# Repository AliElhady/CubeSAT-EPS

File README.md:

# CubeSAT-EPS
CubeSat Electrical Power System (EPS)

This project is a custom Electrical Power System for a CubeSat-class satellite, designed from scratch around a 2-cell Li-ion battery pack, solar input, and an STM32G474 microcontroller for smart power management and telemetry.

The EPS handles everything from harvesting solar energy, to charging and protecting the battery, to distributing clean, regulated rails to the rest of the satellite and streaming live power data to a ground station over LoRa.

Key Features

⚡ Solar Energy Harvesting & Battery Charging

MPPT-based solar charger (BQ24650 class) for 2S Li-ion pack
Supports simultaneous battery charging and system load powering
Automatic priority: uses solar power when available, falls back to battery when not

🔋 Battery Management & Protection

2-cell Li-ion battery pack with BMS for over-charge, over-discharge and over-current protection
Ideal-diode & reverse-polarity MOSFET circuitry on the battery input
TVS + LC filtering on critical power rails

📏 Power Monitoring & Telemetry

Multiple INA226 current/voltage monitors on battery, solar input, and main rails
Real-time telemetry sent via DL-SX1278PA LoRa module to a ground station
Designed for logging battery voltage, current, power, and solar harvesting performance

🧠 Control & Housekeeping

STM32G474RE microcontroller for EPS control, data acquisition, and LoRa communication
5 V and 3.3 V regulated rails for payload, OBC, and communication subsystems
Fault monitoring hooks for future safe-mode / load-shedding logic

🛠️ Hardware-Focused Design

KiCad-based 4-layer PCB (EPS + LoRa + sensing on a single board)
U.FL RF connector with optional π-network pads for antenna matching
Designed as a teaching/learning platform for small-sat power electronics

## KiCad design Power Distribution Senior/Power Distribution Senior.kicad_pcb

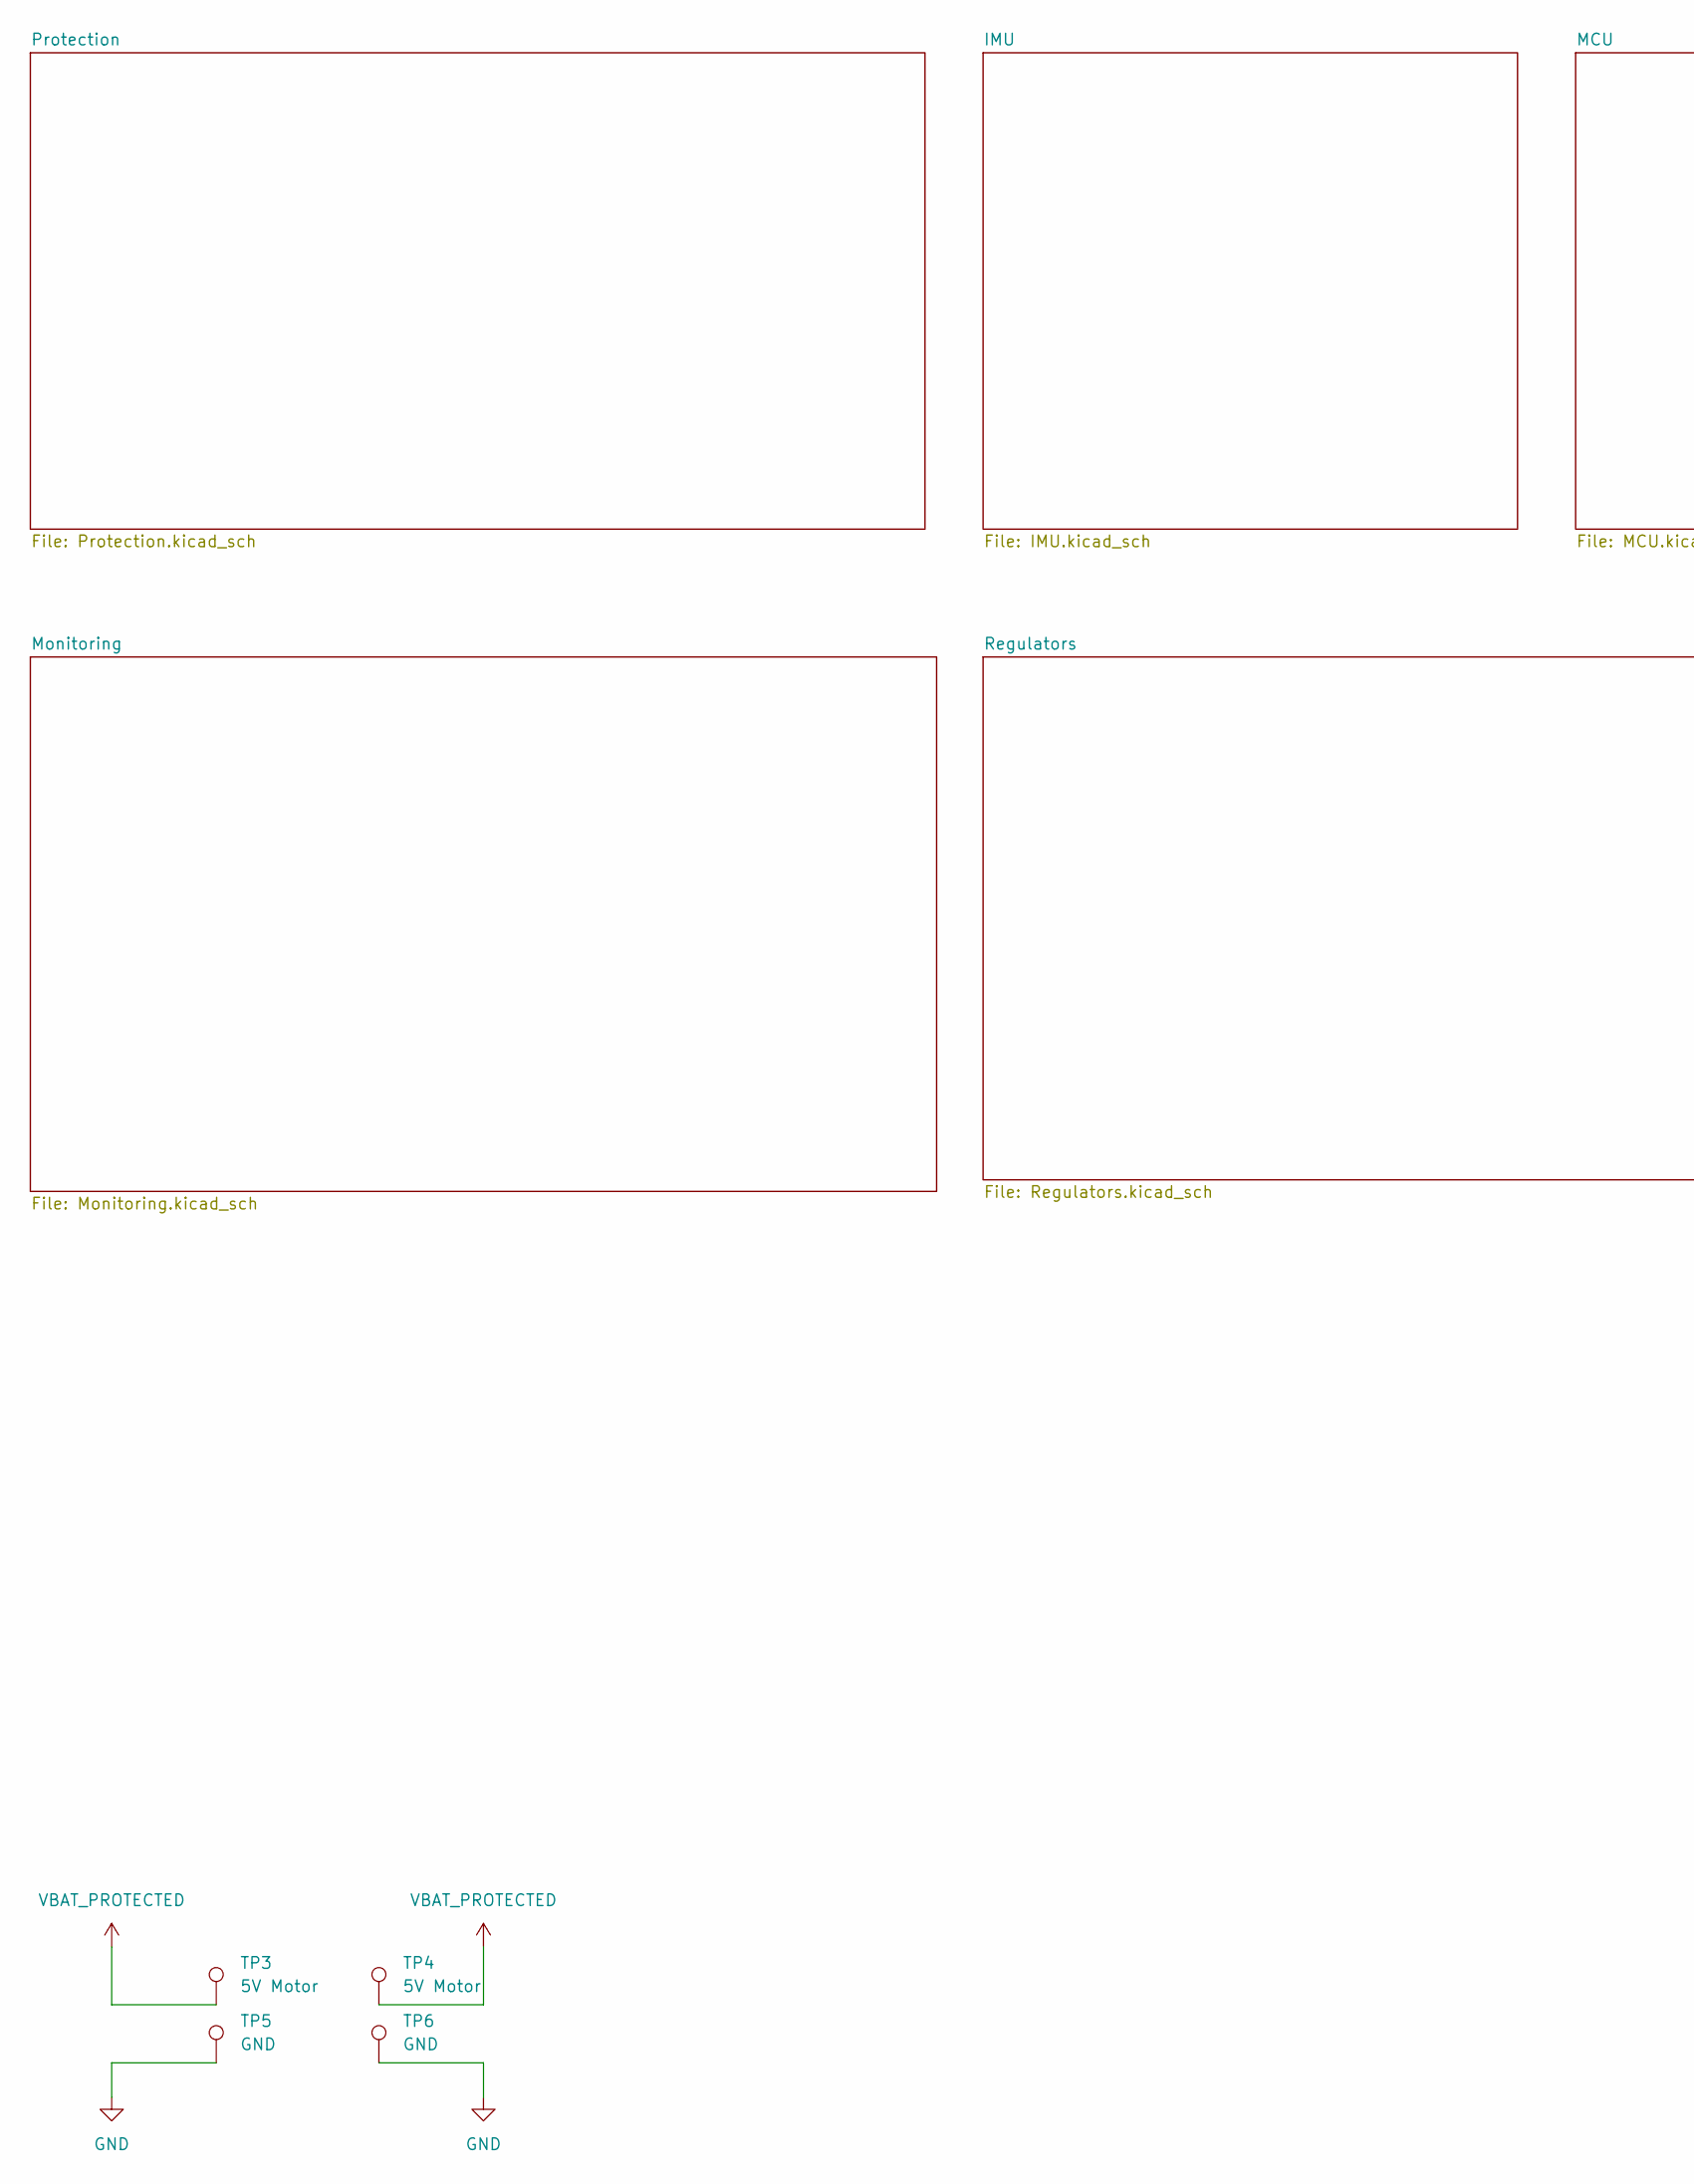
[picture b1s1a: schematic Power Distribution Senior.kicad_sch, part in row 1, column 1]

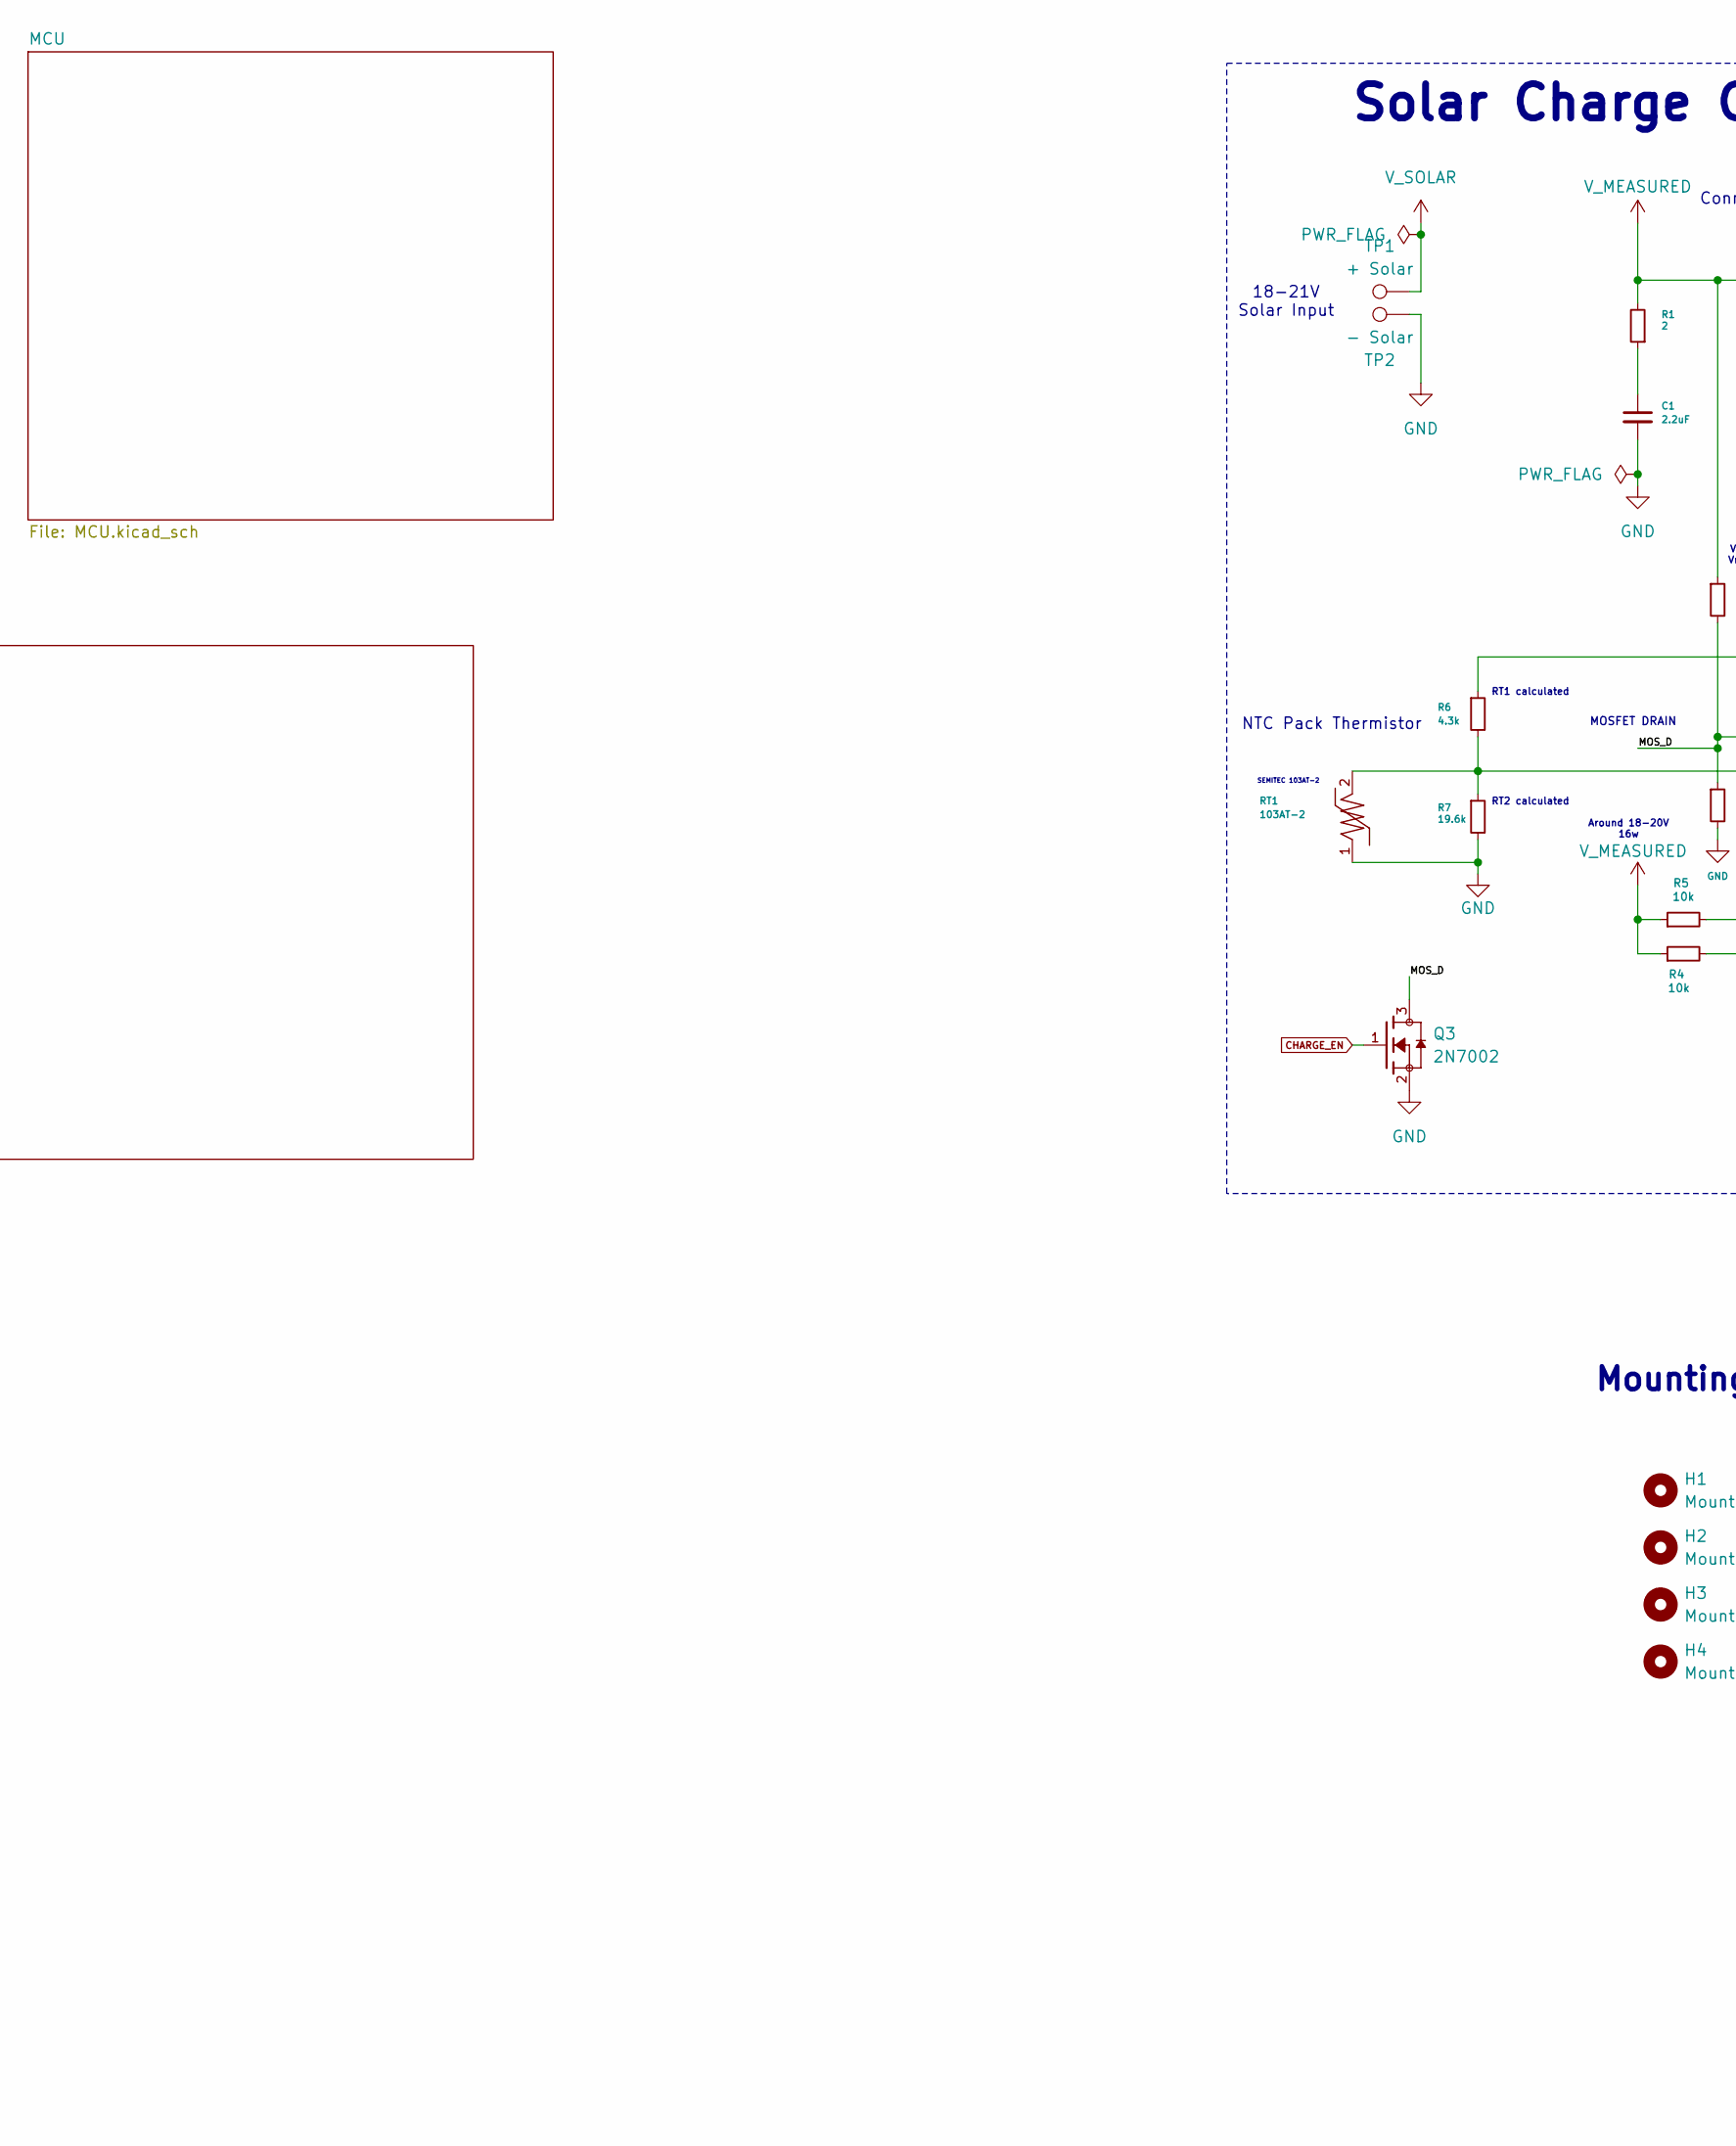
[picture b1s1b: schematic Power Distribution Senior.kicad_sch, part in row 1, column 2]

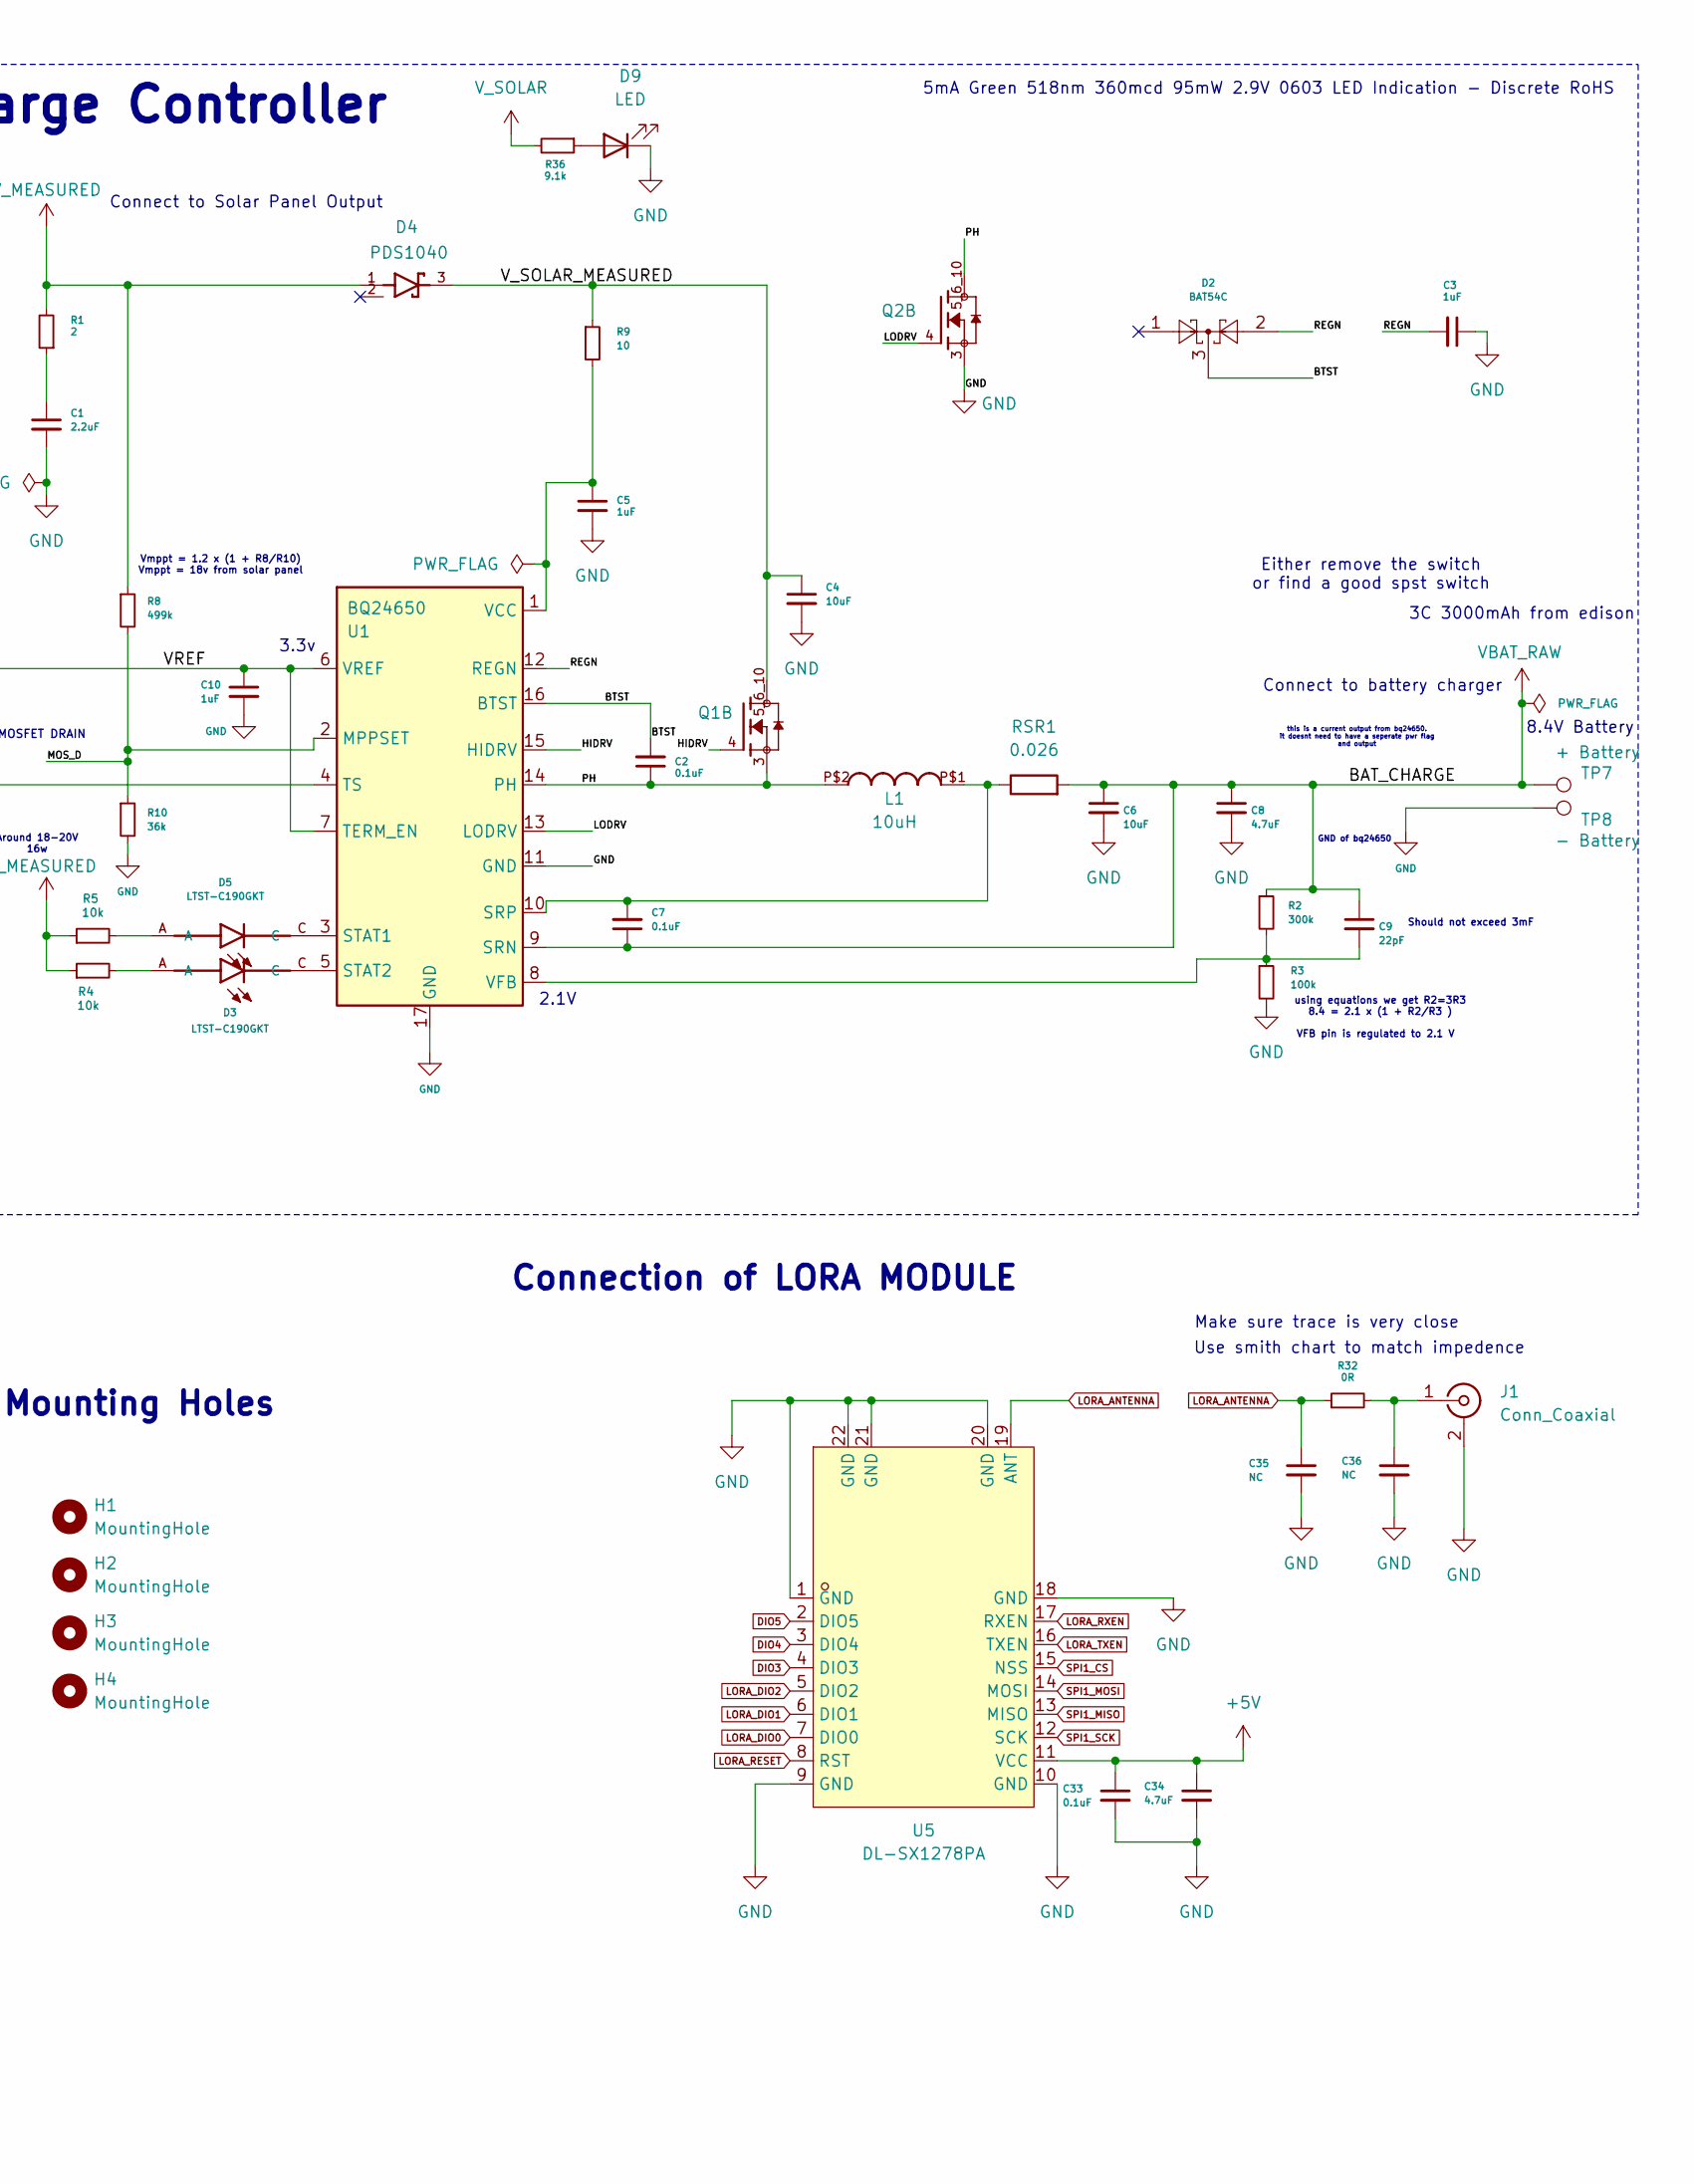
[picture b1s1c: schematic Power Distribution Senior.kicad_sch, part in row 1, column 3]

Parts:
C1: 2.2uF; C_1206_3216Metric
C2, C7: 0.1uF; C_0805_2012Metric
C3, C5, C10: 1uF; C_0805_2012Metric
C4, C6: 10uF; C_0805_2012Metric
C8, C34: 4.7uF; C_1206_3216Metric
C9: 22pF; C_0402_1005Metric
C33: 0.1uF; C_0603_1608Metric
C35, C36: NC; C_0603_1608Metric
D2: BAT54C; SOT-23
D3, D5: LTST-C190GKT; LEDM1608X80
D4: PDS1040; DIO_PDS1040; PARTREV 13
D9: LED; LED_0603_1608Metric
H1, H2, H3, H4: MountingHole; MountingHole_3.2mm_M3_DIN965_Pad
J1: Conn_Coaxial; RF-SMD_FRF05002-JSS103M
L1: 10uH; 2525
Q1, Q2: SI7288DP-T1-GE3; TRANS_SI7288DP-T1-GE3; PARTREV A
Q3: 2N7002; TRANS_2N7002; PARTREV 2023-01-11
R1: 2; R_0805_2012Metric
R2: 300k; R_0402_1005Metric
R3: 100k; R_0402_1005Metric
R4, R5: 10k; R_0402_1005Metric
R6: 4.3k; R_0402_1005Metric
R7: 19.6k; R_0402_1005Metric
R8: 499k; R_0402_1005Metric
R9: 10; R_1206_3216Metric
R10: 36k; R_0402_1005Metric
R32: 0R; R_0805_2012Metric
R36: 9.1k; R_0805_2012Metric
RSR1: 0.026; R_2512_6332Metric
RT1: 103AT-2
TP1: + Solar; TestPoint_Pad_4.0x4.0mm
TP2: - Solar; TestPoint_Pad_4.0x4.0mm
TP3, TP4: 5V Motor; TestPoint_Pad_3.0x3.0mm
TP5, TP6: GND; TestPoint_Pad_3.0x3.0mm
TP7: + Battery; TestPoint_Pad_4.0x4.0mm
TP8: - Battery; TestPoint_Pad_4.0x4.0mm
U1: BQ24650; Texas_RVA_VQFN-16-1EP_3.5x3.5mm_P0.5mm_EP2.14x2.14mm_Therma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
U5: DL-SX1278PA; SMD-22_L37.0-W25.0-P2.54-LB; LCSC Part C3345217

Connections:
/BTST: C2.2, D2.3, U1.16 (BTST)
/HIDRV: Q1.4, U1.15 (HIDRV)
/LODRV: Q2.4, U1.13 (LODRV)
/MOS_D: Q3.3, R8.2, R10.1, U1.2 (MPPSET)
/PH: C2.1, L1.P$2, Q1.3, Q2.5_6_10, U1.14 (PH)
/REGN: C3.2, D2.2, U1.12 (REGN)
/VREF: C10.1, R6.1, U1.6 (VREF), U1.7 (TERM_EN)
/V_SOLAR_MEASURED: C4.1, D4.3, Q1.5_6_10, R9.1
CHARGE_EN: Q3.1; also elsewhere on the board
DIO3: U5.4 (DIO3)
DIO4: U5.3 (DIO4)
DIO5: U5.2 (DIO5)
GND: C1.2, C3.1, C4.2, C5.2, C6.2, C8.2, C10.2, C33.2, C34.2, C35.2, C36.2, D9.1 (K), J1.2 (Ext), Q2.3, Q3.2, R3.2, R7.2, R10.2, RT1.1, TP2.1, TP5.1, TP6.1, TP8.1, U1.11 (GND), U1.17 (GND), U5.1 (GND), U5.9 (GND), U5.10 (GND), U5.18 (GND), U5.20 (GND), U5.21 (GND), U5.22 (GND); also elsewhere on the board
INA226_VS: C33.1, C34.1, U5.11 (VCC); also elsewhere on the board
LORA_ANTENNA: C35.1, R32.1, U5.19 (ANT)
LORA_DIO0: U5.7 (DIO0); also elsewhere on the board
LORA_DIO1: U5.6 (DIO1); also elsewhere on the board
LORA_DIO2: U5.5 (DIO2); also elsewhere on the board
LORA_RESET: U5.8 (RST); also elsewhere on the board
LORA_RXEN: U5.17 (RXEN); also elsewhere on the board
LORA_TXEN: U5.16 (TXEN); also elsewhere on the board
unnamed: C1.1, R1.1
unnamed: D3.A, R4.2
unnamed: D5.A, R5.2
unnamed: D9.2 (A), R36.1
unnamed: C36.1, J1.1 (In), R32.2
unnamed: C7.2, L1.P$1, RSR1.1, U1.10 (SRP)
unnamed: D5.C, U1.3 (STAT1)
unnamed: D3.C, U1.5 (STAT2)
unnamed: R6.2, R7.1, RT1.2, U1.4 (TS)
unnamed: C5.1, R9.2, U1.1 (VCC)
unnamed: C9.2, R2.2, R3.1, U1.8 (VFB)
SPI1_CS: U5.15 (NSS); also elsewhere on the board
SPI1_MISO: U5.13 (MISO); also elsewhere on the board
SPI1_MOSI: U5.14 (MOSI); also elsewhere on the board
SPI1_SCK: U5.12 (SCK); also elsewhere on the board
VBAT_PROTECTED: TP3.1, TP4.1; also elsewhere on the board
VBAT_RAW: C6.1, C7.1, C8.1, C9.1, R2.1, RSR1.2, TP7.1, U1.9 (SRN); also elsewhere on the board
V_MEASURED: D4.1, R1.2, R4.1, R5.1, R8.1; also elsewhere on the board
V_SOLAR: R36.2, TP1.1; also elsewhere on the board

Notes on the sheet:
Solar Charge Controller
VFB pin is regulated to 2.1 V
Use smith chart to match impedence
this is a current output from bq24650. it doesnt need to have a seperate pwr flag and output
RT1 calculated
Around 18-20V 16w
Should not exceed 3mF
NTC Pack Thermistor
3C 3000mAh from edison
Vmppt = 1.2 x (1 + R8/R10) Vmppt = 18v from solar panel
GND of bq24650
RT2 calculated
Connect to Solar Panel Output
Connection of LORA MODULE
Connect to battery charger
3.3v
5mA Green 518nm 360mcd 95mW 2.9V 0603 LED Indication - Discrete RoHS
18-21V Solar Input
Mounting Holes
using equations we get R2=3R3 8.4 = 2.1 x (1 + R2/R3 )
MOSFET DRAIN
2.1V
Make sure trace is very close
SEMITEC 103AT-2
8.4V Battery
Either remove the switch or find a good spst switch

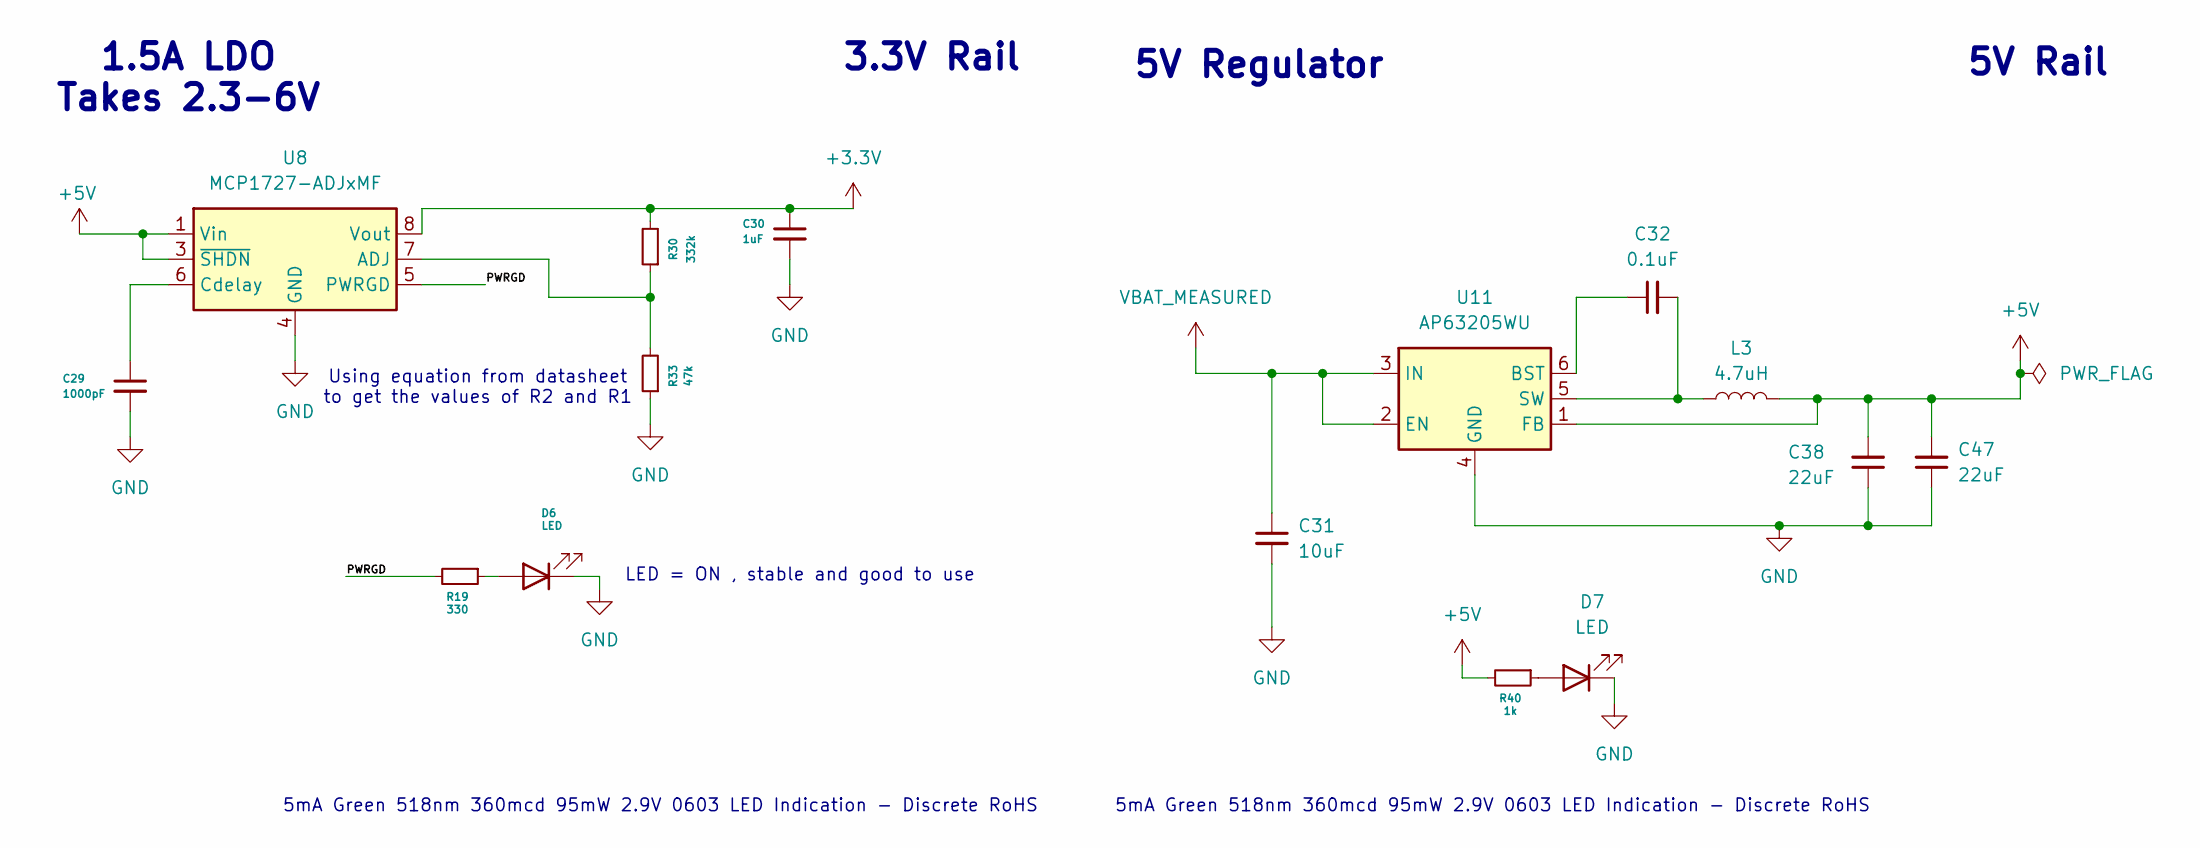
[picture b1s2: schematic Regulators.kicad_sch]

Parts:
C29: 1000pF; C_0805_2012Metric
C30: 1uF; C_0805_2012Metric
C31: 10uF; C_0805_2012Metric
C32: 0.1uF; C_0805_2012Metric
C38: 22uF; C_0805_2012Metric
C47: 22uF; C_0603_1608Metric
D6, D7: LED; LED_0603_1608Metric
L3: 4.7uH; L_Vishay_IFSC-1515AH_4x4x1.8mm
R19: 330; R_0402_1005Metric
R30: 332k; R_0402_1005Metric
R33: 47k; R_0402_1005Metric
R40: 1k; R_0805_2012Metric
U8: MCP1727-ADJxMF; DFN-8-1EP_3x3mm_P0.65mm_EP1.55x2.4mm
U11: AP63205WU; TSOT-23-6

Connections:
+3.3V: C30.1, R30.2, U8.8 (Vout); also elsewhere on the board
/Regulators/PWRGD: R19.2, U8.5 (PWRGD)
GND: C29.2, C30.2, C31.2, C38.1, C47.1, D6.1 (K), D7.1 (K), R33.1, U8.4 (GND), U8.9 (GND), U11.4 (GND); also elsewhere on the board
INA226_VS: C38.2, C47.2, L3.2, R40.2, U8.1 (Vin), U8.2 (Vin), U8.3 (~SHDN), U11.1 (FB); also elsewhere on the board
unnamed: D6.2 (A), R19.1
unnamed: D7.2 (A), R40.1
unnamed: R30.1, R33.2, U8.7 (ADJ)
unnamed: C29.1, U8.6 (Cdelay)
unnamed: C32.1, U11.6 (BST)
unnamed: C32.2, L3.1, U11.5 (SW)
VBAT_MEASURED: C31.1, U11.2 (EN), U11.3 (IN); also elsewhere on the board

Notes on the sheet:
1.5A LDO Takes 2.3-6V
5V Rail
LED = ON , stable and good to use
5mA Green 518nm 360mcd 95mW 2.9V 0603 LED Indication - Discrete RoHS
3.3V Rail
Using equation from datasheet to get the values of R2 and R1
5V Regulator

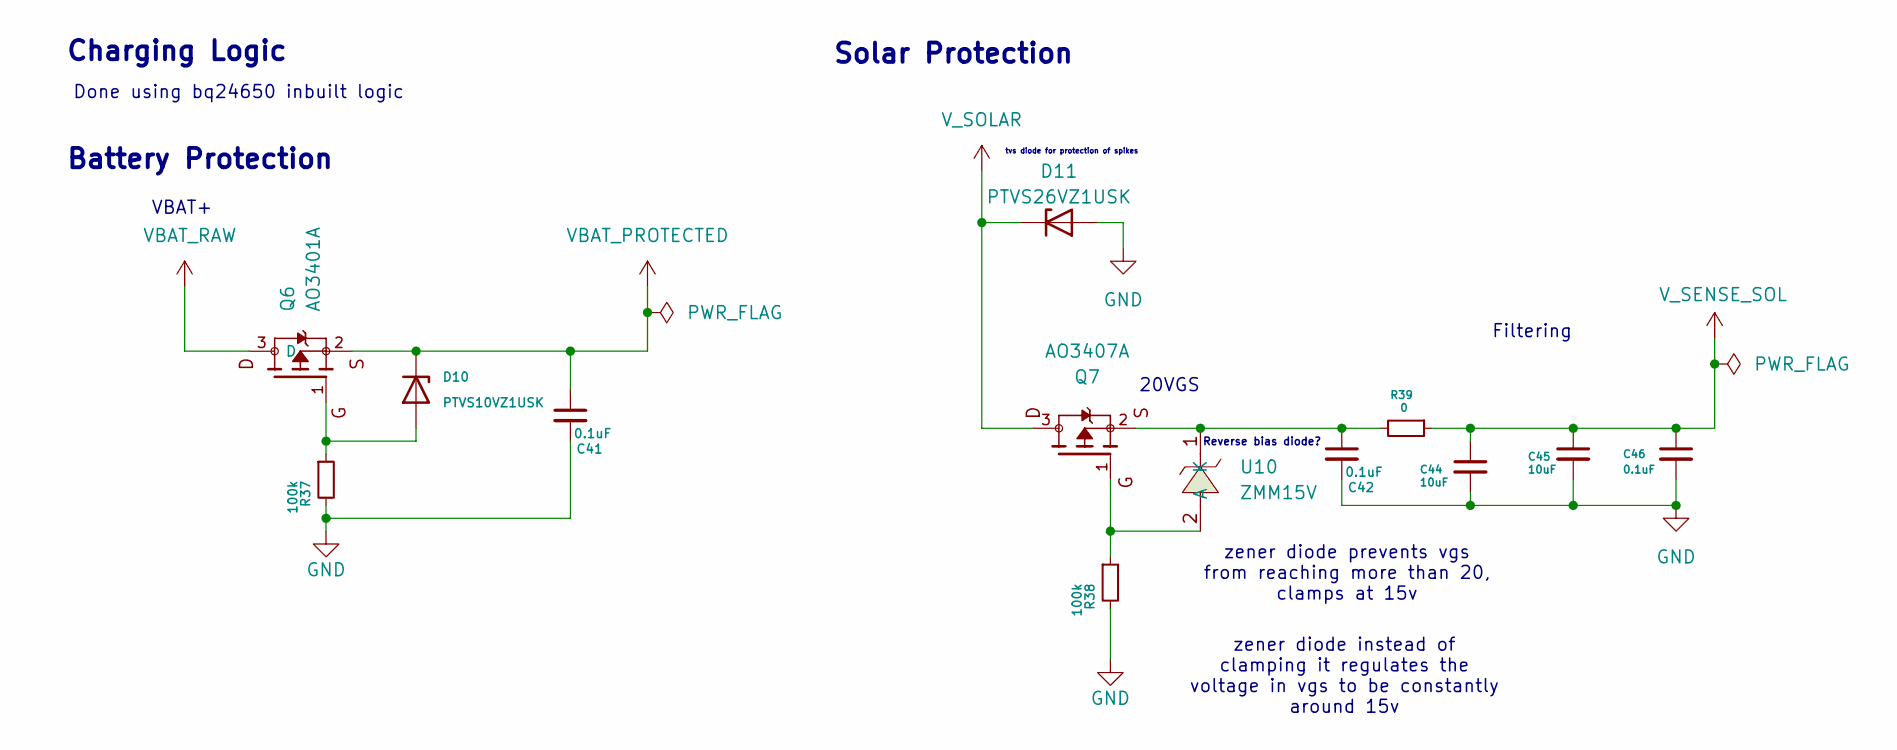
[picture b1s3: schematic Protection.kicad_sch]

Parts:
C41, C42, C46: 0.1uF; C_0603_1608Metric
C44, C45: 10uF; C_0805_2012Metric
D10: PTVS10VZ1USK; Nexperia_DSN1608-2_1.6x0.8mm
D11: PTVS26VZ1USK; Nexperia_DSN1608-2_1.6x0.8mm
Q6: AO3401A; SOT23-3
Q7: AO3407A; SOT95P280X125-3N; PARTREV 5
R37, R38: 100k; R_0805_2012Metric
R39: 0; R_0805_2012Metric
U10: ZMM15V; LL-34_L3.5-W1.5-RD; LCSC Part C5346000

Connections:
GND: C41.2, C42.2, C44.2, C45.2, C46.2, D11.2 (A), R37.2, R38.2; also elsewhere on the board
unnamed: D10.2 (A), Q6.1, R37.1
unnamed: Q7.1, R38.1, U10.2 (A)
unnamed: C42.1, Q7.2, R39.2, U10.1 (K)
VBAT_PROTECTED: C41.1, D10.1 (K), Q6.2; also elsewhere on the board
VBAT_RAW: Q6.3 (D); also elsewhere on the board
V_SENSE_SOL: C44.1, C45.1, C46.1, R39.1; also elsewhere on the board
V_SOLAR: D11.1 (K), Q7.3; also elsewhere on the board

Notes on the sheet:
Reverse bias diode?
20VGS
zener diode instead of clamping it regulates the voltage in vgs to be constantly around 15v
Done using bq24650 inbuilt logic
Charging Logic
Battery Protection
VBAT+
Filtering
zener diode prevents vgs from reaching more than 20, clamps at 15v
tvs diode for protection of spikes
Solar Protection

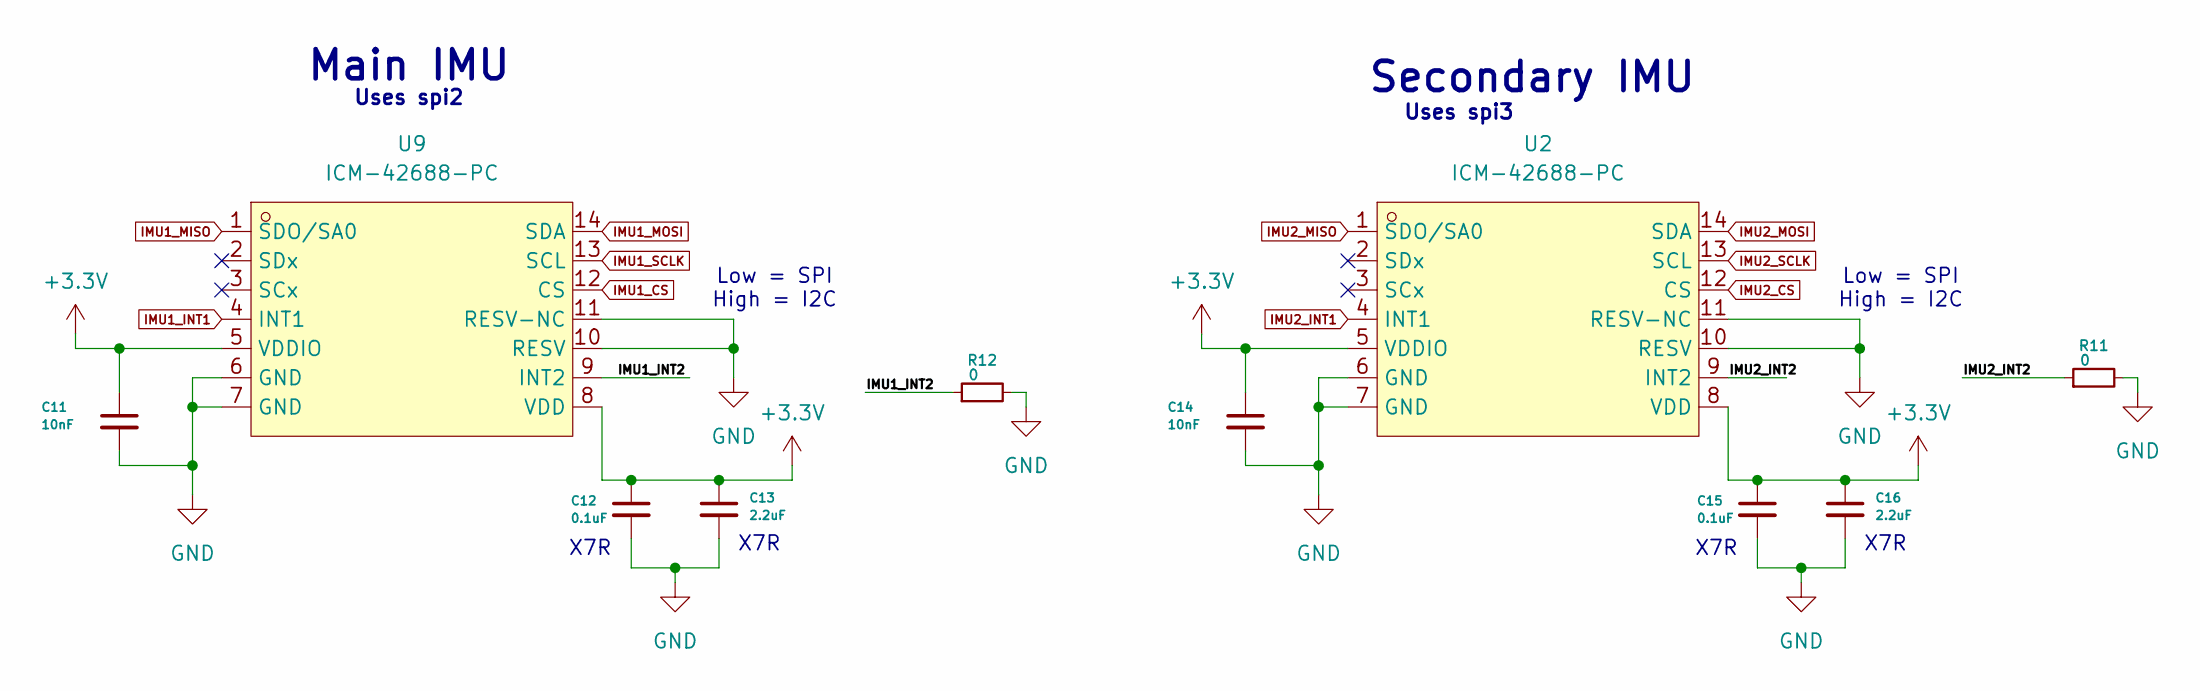
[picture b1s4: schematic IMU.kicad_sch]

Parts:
C11, C14: 10nF; C_0402_1005Metric
C12, C15: 0.1uF; C_0402_1005Metric
C13, C16: 2.2uF; C_0402_1005Metric
R11, R12: 0; R_0805_2012Metric
U2, U9: ICM-42688-PC; LGA-14_L3.0-W2.5-P0.50-TL; LCSC Part C48586483

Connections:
+3.3V: C11.1, C12.1, C13.1, C14.1, C15.1, C16.1, U2.5 (VDDIO), U2.8 (VDD), U9.5 (VDDIO), U9.8 (VDD); also elsewhere on the board
/IMU/IMU1_INT2: R12.1, U9.9 (INT2)
/IMU/IMU2_INT2: R11.1, U2.9 (INT2)
GND: C11.2, C12.2, C13.2, C14.2, C15.2, C16.2, R11.2, R12.2, U2.6 (GND), U2.7 (GND), U2.10 (RESV), U2.11 (RESV-NC), U9.6 (GND), U9.7 (GND), U9.10 (RESV), U9.11 (RESV-NC); also elsewhere on the board
IMU1_CS: U9.12 (CS); also elsewhere on the board
IMU1_INT1: U9.4 (INT1); also elsewhere on the board
IMU1_MISO: U9.1 (SDO/SA0); also elsewhere on the board
IMU1_MOSI: U9.14 (SDA); also elsewhere on the board
IMU1_SCLK: U9.13 (SCL); also elsewhere on the board
IMU2_CS: U2.12 (CS); also elsewhere on the board
IMU2_INT1: U2.4 (INT1); also elsewhere on the board
IMU2_MISO: U2.1 (SDO/SA0); also elsewhere on the board
IMU2_MOSI: U2.14 (SDA); also elsewhere on the board
IMU2_SCLK: U2.13 (SCL); also elsewhere on the board

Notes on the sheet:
Uses spi3
X7R
Low = SPI High = I2C
Uses spi2
Main IMU
Secondary IMU
